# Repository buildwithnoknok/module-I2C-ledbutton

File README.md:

# noknok LED Button

A compact I²C‑controlled button module with integrated RGB LED backlight for the noknok ecosystem.  
Designed for user input, menu navigation, and illuminated UI feedback in modular builds.

---

## Overview

The **noknok LED Button** uses a **CH32V003F4U6** microcontroller to read a tactile push button and drive an **SK6812MINI-E** RGB LED via SPI+DMA. It connects to the Raspberry Pi Pico (Conductor) over the standard noknok **JST SH 4‑pin I²C connector**.

The I²C address is assigned dynamically at boot — no conflicts when using multiple modules on the same bus.

Typical use cases:
- Menu selection (OK / Back / Cancel)
- Illuminated status indicators
- Multi‑button control panels
- Confirm actions with colour feedback

---

## Features

- Dynamic I²C address via noknok enumeration protocol (no hardcoded address)
- CH32V003F4U6 microcontroller (RISC‑V, 48 MHz, QFN-20)
- SK6812MINI-E RGB LED (SPI + DMA driven — CPU-free updates)
- Tactile push button with 20 ms hardware debounce
- Press edge, release edge, and cumulative press count — no polling gaps
- 3.3V operation via noknok I²C connector
- Compact 20×20 mm PCB

---

## I²C Protocol

**I²C address:** assigned dynamically at boot — see [Enumeration](#enumeration).

### Commands (Pico → Module)

| Bytes | Command | Description |
|-------|---------|-------------|
| `0x00` | **LED OFF** | Turn LED off immediately |
| `0x10` `R` `G` `B` `0x00` | **SET COLOR** | Set LED colour (R, G, B each 0–255) |
| `0x11` | **RESET COUNT** | Reset cumulative press counter to 0 |
| `0xB0` | **ENTER BOOTLOADER** | Reset into the I²C bootloader for an over‑the‑wire firmware update (see [Firmware](#firmware)) |
| `0xB1` | **GET VERSION** | Standard noknok command — the next read returns 4 version bytes (see below) |

### Version read (Pico ← Module)

`GET_VERSION` (`0xB1`) is a **noknok ecosystem-standard** command (the `0xB0`–`0xBF` range is reserved for standard commands across every module). Write `0xB1`, then read **4 bytes**: `[PROTOCOL_VERSION, FW_MAJOR, FW_MINOR, FW_PATCH]` = `[0x01, 2, 2, 0]`. Lets the Conductor compare the installed version against the version required by the product manifest. **→ Full spec:** [Ecosystem / software / readme.md §5](https://github.com/buildwithnoknok/Ecosystem/blob/main/software/readme.md#5-standard-system-commands)

### Status read (Pico ← Module)

Read **2 bytes**:

**Byte 0 — status flags:**

| Bit | Meaning |
|-----|---------|
| 0 | Button currently pressed (`1` = held down) |
| 1 | Press event since last read (edge, auto-clears) |
| 2 | Release event since last read (edge, auto-clears) |

**Byte 1 — cumulative press count** (0–255, wraps)

> Edge flags (bits 1 and 2) are cleared on the module after each read. Poll at ~50 ms and you won't miss any press or release.

---

## Enumeration

The module uses the standard noknok dynamic enumeration protocol — no hardcoded I²C address. At boot it flashes the LED white briefly, then counts a UID-derived backoff delay before joining the bus at `0x7F` for address assignment. On successful assignment, the LED flashes green.

**→ Full protocol spec:** [Ecosystem / software / enumeration.md](https://github.com/buildwithnoknok/Ecosystem/blob/main/software/enumeration.md)

---

## Python API

Use the `noknok.py` library from the [Ecosystem repo](https://github.com/buildwithnoknok/Ecosystem/tree/main/software/pico) on the Pico.

```python
from noknok import Conductor

c = Conductor()        # GP8 = SDA, GP9 = SCL
c.enumerate()          # discover all modules (~3 s)

kb = c.ledbutton[0]             # first LED Button by discovery order
# or: kb = c.role["ok_button"]  # by role name after setup_roles()

# LED control
kb.set_color(255, 0, 0)         # red
kb.set_color(0, 255, 0)         # green
kb.set_color(255, 255, 255)     # white
kb.led_off()

# Button reading — returns LedButtonStatus or None on I2C error
s = kb.read()
if s is not None:
    print(s.pressed)        # True if held right now
    print(s.press_event)    # True if pressed since last read
    print(s.release_event)  # True if released since last read
    print(s.count)          # cumulative press count (0–255)

# Reset counter
kb.reset_count()
```

---

## Hardware

| Spec | Value |
|------|-------|
| PCB size | 20 × 20 mm |
| MCU | CH32V003F4U6 (QFN‑20, RISC‑V, 48 MHz) |
| LED | SK6812MINI-E (RGB, SPI-driven) |
| Button | Tactile switch, active LOW, internal pull-up |
| Connector | JST SH 4‑pin (Qwiic / STEMMA QT compatible) |
| Supply voltage | 3.3V via I²C connector |
| LED data pin | PC6 (SPI1 MOSI, DMA-driven) |
| Button pin | PD4 (active LOW) |
| I²C SDA | PC1 |
| I²C SCL | PC2 |
| Flash header | J3 — 3-pad pogo (GND, SWIO, VCC), noknok M2.5-keyed footprint. SWIO/PD1 also carries the status LED (D4, active LOW). |
| Hardware version | v2.0 |

---

## Firmware

**v2.4 runs under the shared noknok I²C bootloader** ([module-I2C-bootloader](https://github.com/buildwithnoknok/module-I2C-bootloader)), so the module can be re‑flashed **over the I²C bus** — no SWDIO cable needed in the field.

Flash map (16 KB):

| Region | Address | Written by |
|--------|---------|-----------|
| Bootloader — stage-0 (1 KB, frozen) + stage-1 (4 KB, OTA-updatable) | `0x0000` | SWD, **once** at manufacture |
| Application (this firmware) | `0x1400` | I²C OTA |
| Metadata (validity marker) | `0x3FC0` | I²C OTA |

The application is linked at the `0x1400` offset (`app.ld`, bootloader layout 2) and reserves the top 16 bytes of RAM for the bootloader handoff cell. Command `0xB0` drops the running module back into the bootloader for an update.

### Build

```bash
cd firmware/src
make build   # compile the offset-linked application -> keyboard_firmware.bin
```

> ch32fun must be installed at `../ch32fun/` relative to `firmware/src/` — see [cnlohr/ch32v003fun](https://github.com/cnlohr/ch32v003fun) for setup.

### Flashing

- **Normal (over I²C):** flash `keyboard_firmware.bin` from the Pico using the noknok flasher (`module_flasher.py` in `brain-Pico`). No cable.
- **First time / blank board:** SWD‑flash the bootloader once (`make flash` in the bootloader repo), then flash this app over I²C.
- **Backup / recovery (SWD):** the 5‑pin SWIO header is the unbrickable backstop — see *Recovery & SWD flashing* in the [bootloader README](https://github.com/buildwithnoknok/module-I2C-bootloader#recovery--swd-flashing).

`make flash` here still does a one‑off SWD flash of the app for bench bring‑up if you need it.

| Metric | Value |
|--------|-------|
| Firmware version | v2.4.1 (bootloader‑hosted, app base `0x1400`) |
| Application size | 3144 B (of the 10 KB app region) |

---

## Changelog

### Hardware v2.0 — status LED, pogo flash pads, no on-board pull-ups
Status LED on PD1/SWIO, castellated edges replaced with 3-pad pogo flashing pads (J3), on-board I²C pull-ups removed (host-only now). Full change record: [hardware/readme.md](hardware/readme.md#hardware-change-record).

### v2.4.1 — version bump only (firmware-index bring-up)
No functional change. Cut purely to give the new firmware-index OTA path a real installed-vs-current delta to exercise end to end (resolve → bootloader gate → fetch → flash → verify). Identical to v2.4.0 apart from the `GET_VERSION` patch byte. Ships alongside the first [`firmware/index.json`](firmware/index.json), which is how the brain now discovers the current firmware for this module — see [Ecosystem / software / firmware-index.md](https://github.com/buildwithnoknok/Ecosystem/blob/main/software/firmware-index.md).

### v2.4.0 — app base 0x1400 (bootloader layout 2)
Relinked at the `0x1400` flash offset (bootloader **layout 2**: 1 KB stage-0 + 4 KB stage-1 below the app; was `0x1000`). Firmware behaviour unchanged. **Not compatible with the legacy monolithic bootloader or a layout-1 stage-1** — such a module gets stage-0 + stage-1 v1.1.0 over SWD first, then this app over I²C. See [module-I2C-bootloader](https://github.com/buildwithnoknok/module-I2C-bootloader).

### v2.3.0 — watchdog + boot-health handshake (DEV-31)
Runs the independent watchdog (~2 s, kicked every main-loop pass) and writes `0` to `0x200007F8` the moment its I²C address is assigned — the app-health handshake with the stage-1 bootloader. Stage-1 counts watchdog resets and parks the module (error 7, rescued by the Conductor by UID) after three in a row, instead of booting a broken app forever. Contract: [Ecosystem / software / bootloader-update.md §3](https://github.com/buildwithnoknok/Ecosystem/blob/main/software/bootloader-update.md). No protocol or command change.

### v2.2.0 — SK6812 LED driver fix
Replaced the hand-rolled SPI+DMA SK6812 driver with cnlohr's proven
[`ws2812b_dma_spi_led_driver.h`](https://github.com/cnlohr/ch32fun/blob/master/extralibs/ws2812b_dma_spi_led_driver.h)
(ch32fun `extralibs`). The old driver produced a **marginal waveform** that
genuine-but-less-tolerant SK6812 lots misread — one batch showed wrong colours
(a spurious green channel) on ~13 of 20 units. This was **initially misdiagnosed
as bad/counterfeit LEDs; the LEDs are genuine OPSCO** — the fault was our driver.
The library produces a clean, glitch-free waveform. Four concrete differences vs.
the old driver:

- **16-bit SPI** transfers (was 8-bit) — cleaner framing, fewer inter-word gaps
- **`SPI1->HSCR = 1`** high-speed read mode (was not set)
- **`DMA_Priority_VeryHigh`** (was medium) — prevents inter-byte gaps under bus contention
- **`SPI1->DATAR = 0`** to force the data line low before the first frame (kills the start-of-frame glitch)

Still DMA (no bit-bang), so it never blocks the I²C / TIM2 interrupts. Wire order
(G, R, B) and the I²C command set are unchanged, so it's a drop-in OTA update.

### v2.1.0 — bootloader-hosted
Offset-linked at `0x1400` to run under the shared noknok I²C bootloader, enabling
I²C OTA firmware updates. Added the `GET_VERSION` (`0xB1`) standard command.

---

## Status

| Area | Status |
|------|--------|
| Hardware | v2.0 complete |
| Firmware | **v2.2 — complete (bootloader‑hosted, I²C OTA bench‑proven)** |
| Python library | **complete** (in [Ecosystem repo](https://github.com/buildwithnoknok/Ecosystem/tree/main/software/pico)) |
| Documentation | **complete** |

---

## License

- Firmware / code: MIT — see [LICENSE](LICENSE).
- Hardware (schematics, PCB layout, fab files): CC BY-SA 4.0 — see [LICENSE-hardware](LICENSE-hardware).

## Trademarks

**noknok** is a registered trademark in Switzerland (Swissreg 1300007033).

Qwiic is a registered trademark of SparkFun Electronics, Inc. STEMMA QT is a
trademark of Adafruit Industries, LLC. Both are named here only to state
connector compatibility - noknok is not affiliated with, endorsed by, or
sponsored by either company.
---

---

## Safety & Liability

noknok hardware is an electronic device and a DIY/maker kit. You assemble, modify, flash, power, and operate it at your own risk, and it is provided as is, without warranty. See the full notice: [License, Safety & Liability](https://buildwithnoknok.github.io/safety-and-license/).

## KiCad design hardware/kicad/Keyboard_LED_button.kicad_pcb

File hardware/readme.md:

# Hardware — noknok LED Button

Hardware design files for the noknok LED Button module (CH32V003F4U6 — I2C tactile button with RGB LED backlight).

- KiCad project: `kicad/Keyboard_LED_button.*`
- Schematic (PDF): `module-I2C-LEDButton_Schematics.pdf`
- BOM: `module_I2C-LEDButton.xls`
- Board renders: `module-I2C-ledbutton-front.png`, `module-I2C-ledbutton-back.png` *(pre-V2 renders — pending re-export)*

Hardware is licensed CC BY-SA 4.0 (see `../LICENSE-hardware`). Connector, flashing and mounting standards follow the [noknok Ecosystem guidelines](https://github.com/buildwithnoknok/Ecosystem) (electrical + mechanical).

---

## Hardware Change Record

### v2.0 — changes from v1.1
- **Status indicator LED on PD1** (in parallel with the SWIO flashing line — zero extra GPIO). Active-low: `+3V3_PROT → R5 (2.2 kΩ) → D4 anode; D4 cathode → PD1/SWIO`. Driven by the bootloader (off = app running, slow pulse = updating/recovering, solid = error). Parts: red 0603 LED (LCSC C2286) + 2.2 kΩ 0603 (LCSC C4190).
- **Removed the castellated edge pads** — both the I2C edge and the flashing edge (unreliable to contact). I2C is via the JST-SH (Qwiic) connectors J1/J2 only.
- **New flashing interface (J3)** — noknok flash pads (`noknok_FlashPads_I2C-module_1x3_M2.5`): 3 single-side SMD pogo pads (GND / SWIO / VCC) plus an embedded M2.5 keyed mounting hole, from the noknok KiCad library in the Ecosystem repo.
- **Second mounting hole (H1)** — plain `noknok_MountingHole_2.5mm_M2.5`, diagonally opposite the flash-pad hole.
- **Removed the on-board I²C pull-up resistors** (previously R1/R2) — pull-ups now live on the host (Conductor), not per module (avoids stacking on the shared bus). The host must provide the bus pull-ups (proposed 3.3 kΩ); a noknok pull-up PCB covers third-party hosts that lack them. See the [I²C Pull-up Resistor Strategy ADR](https://noknokdev.atlassian.net/wiki/spaces/SD/pages/82280449).
- **Remaining resistors renumbered** after the pull-ups were removed (values unchanged): VDD series R3→**R1** (10 Ω, no spike issue), LED current R4→**R2** (300 Ω), boost feedback divider R5/R6→**R3**/**R4** (25 kΩ / 10 kΩ). New status-LED resistor is **R5** (2.2 kΩ, see above).
- D1 (SK6812MINI-E RGB LED, payload), D2 (protection Zener) and D3 (boost-converter Schottky) are unchanged from v1.1.

**Gap vs. Knob/Buzzer V2 docs:** the board renders are still the pre-V2 photos, pending new production units.

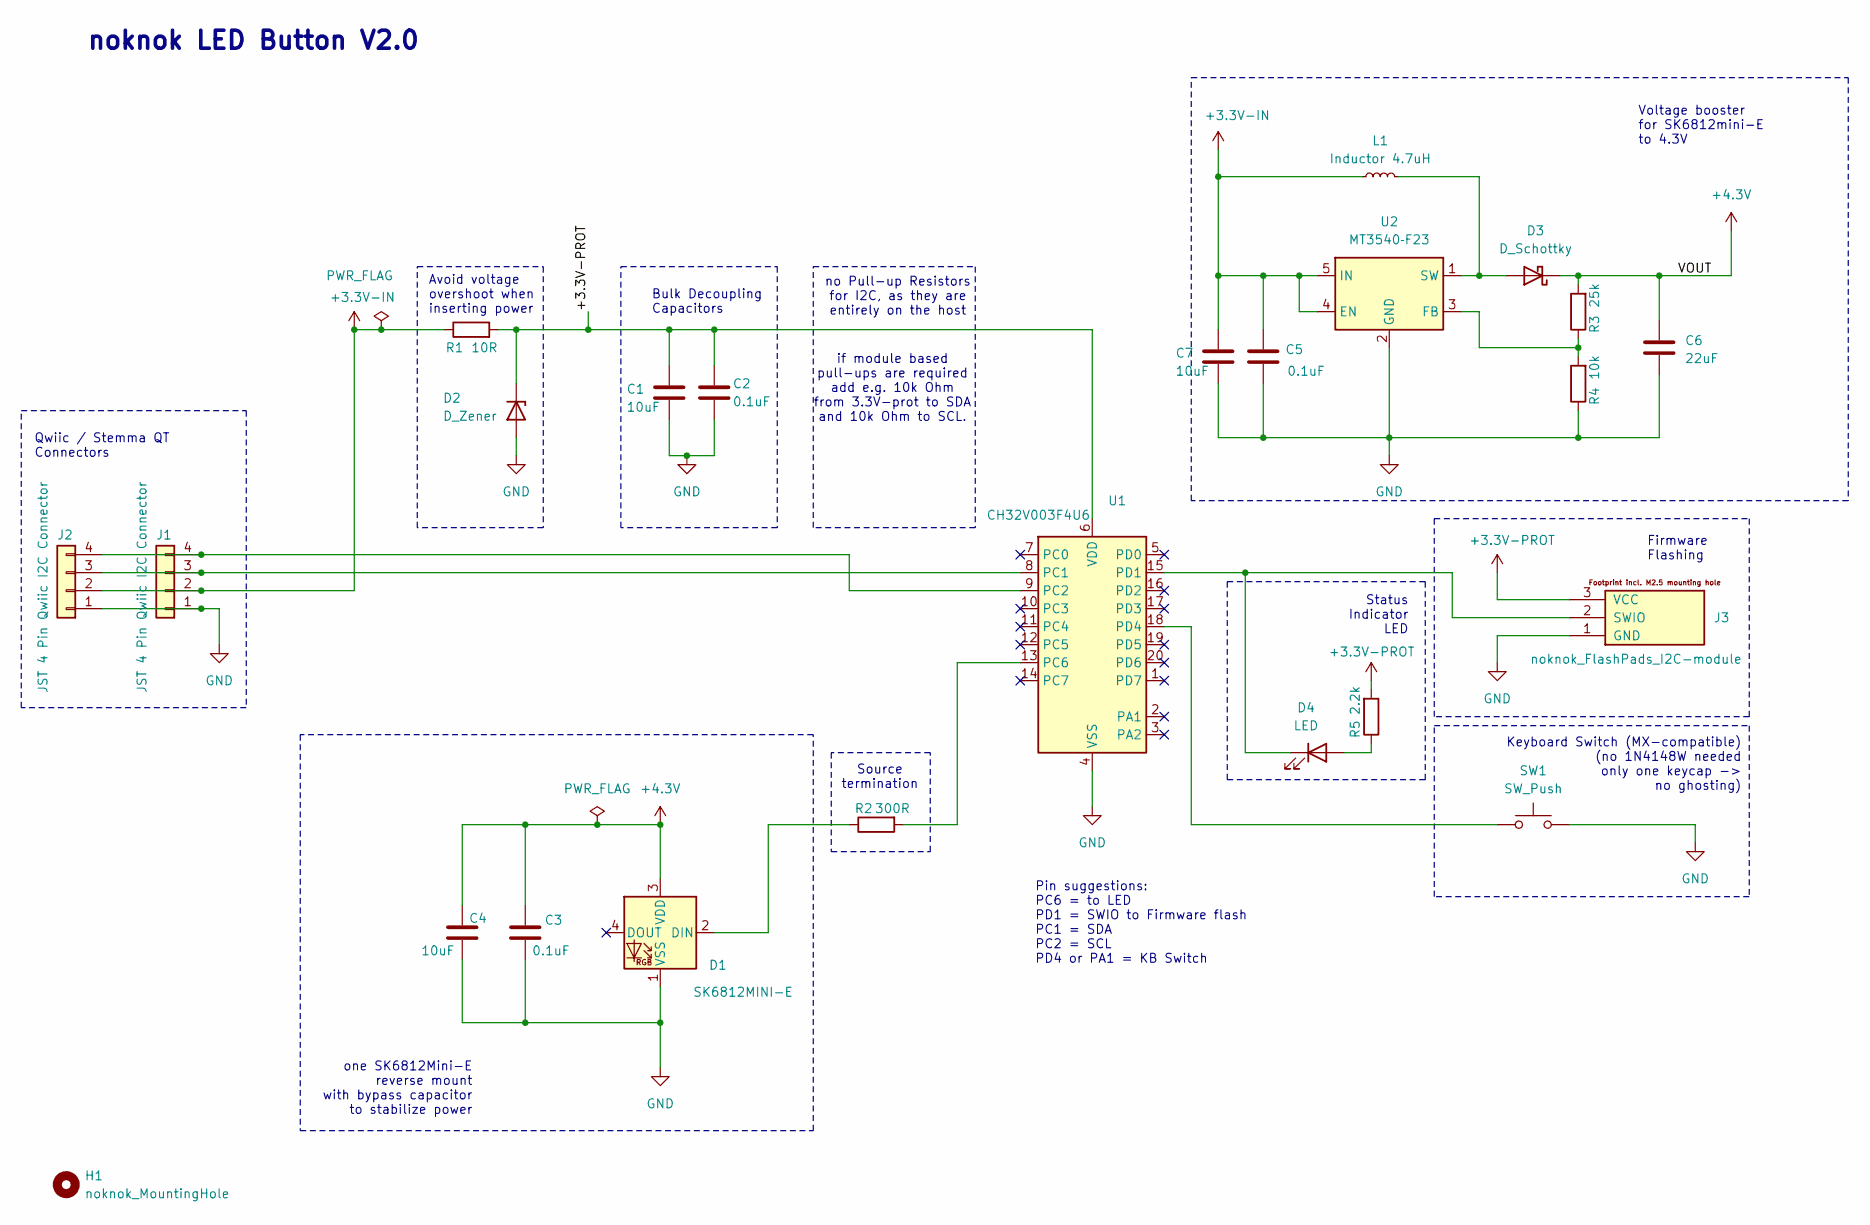
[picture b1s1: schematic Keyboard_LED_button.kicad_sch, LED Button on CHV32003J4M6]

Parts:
C1, C4, C7: 10uF; C_0603_1608Metric
C2, C3, C5: 0.1uF; C_0603_1608Metric
C6: 22uF; C_0603_1608Metric
D1: SK6812MINI-E; LED_SK6812MINI-E_3.2x2.8mm_P1.5mm_ReverseMount
D2: D_Zener; D_SOD-323
D3: D_Schottky; D_SOD-323
D4: LED; LED_0603_1608Metric
H1: noknok_MountingHole; noknok_MountingHole_2.5mm_M2.5
J1, J2: JST 4 Pin Qwiic I2C Connector; JST_SH_SM04B-SRSS-TB_1x04-1MP_P1.00mm_Horizontal
J3: noknok_FlashPads_I2C-module; noknok_FlashPads_I2C-module_1x3_M2.5
L1: Inductor 4.7uH; L_Changjiang_FTC252010S
R1: 10R; R_0603_1608Metric
R2: 300R; R_0603_1608Metric
R3: 25k; R_0603_1608Metric
R4: 10k; R_0603_1608Metric
R5: 2.2k; R_0603_1608Metric
SW1: SW_Push; SW_Cherry_MX_1.00u_PCB_CHRIS
U1: CH32V003F4U6; QFN-20-1EP_3x3mm_P0.4mm_EP1.65x1.65mm
U2: MT3540‑F23; SOT-23-5

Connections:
+3.3V-IN: C5.1, C7.1, J1.2, J2.2, L1.1, R1.1, U2.4 (EN), U2.5 (IN)
+3.3V-PROT: C1.1, C2.1, D2.1 (K), J3.3 (VCC), R1.2, R5.2, U1.6 (VDD)
+4.3V: C3.1, C4.1, C6.1, D1.3 (VDD), D3.1 (K), R3.2
GND: C1.2, C2.2, C3.2, C4.2, C5.2, C6.2, C7.2, D1.1 (VSS), D2.2 (A), J1.1, J2.1, J3.1 (GND), R4.1, SW1.1, U1.4 (VSS), U1.21 (VSS), U2.2 (GND)
unnamed: D1.2 (DIN), R2.1
unnamed: D3.2 (A), L1.2, U2.1 (SW)
unnamed: D4.2 (A), R5.1
unnamed: D4.1 (K), J3.2 (SWIO), U1.15 (PD1)
unnamed: J1.3, J2.3, U1.8 (PC1)
unnamed: J1.4, J2.4, U1.9 (PC2)
unnamed: R2.2, U1.13 (PC6)
unnamed: SW1.2, U1.18 (PD4)
unnamed: R3.1, R4.2, U2.3 (FB)

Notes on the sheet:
Voltage booster for SK6812mini-E to 4.3V
if module based pull-ups are required add e.g. 10k Ohm from 3.3V-prot to SDA and 10k Ohm to SCL.
Avoid voltage overshoot when inserting power
noknok LED Button V2.0
Pin suggestions: PC6 = to LED PD1 = SWIO to Firmware flash PC1 = SDA PC2 = SCL PD4 or PA1 = KB Switch
no Pull-up Resistors for I2C, as they are entirely on the host
Status Indicator LED
Firmware Flashing
Source termination
Qwiic / Stemma QT Connectors
Bulk Decoupling Capacitors
Keyboard Switch (MX-compatible) (no 1N4148W needed only one keycap -> no ghosting)
one SK6812Mini-E reverse mount with bypass capacitor to stabilize power

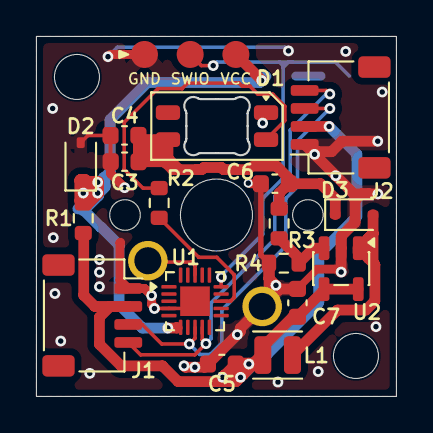
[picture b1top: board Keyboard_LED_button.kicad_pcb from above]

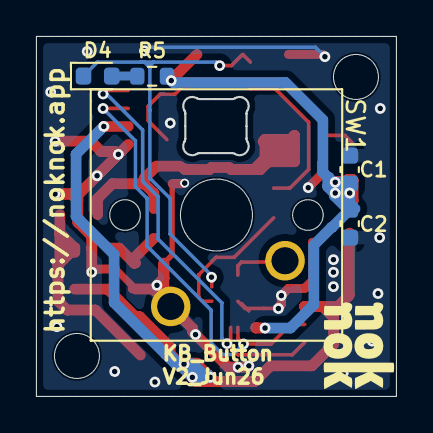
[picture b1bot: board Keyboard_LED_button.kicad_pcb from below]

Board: 2 copper layers, 20.0 x 20.0 mm, 24 parts (5 on the bottom side), 13 nets.

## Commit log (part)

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2026-05-08 Create hardware folder
2026-05-08 add schematics
2026-05-08 Create hardware/kicad folder
2026-05-08 Upload Kicad project files
2026-05-08 Create firmware folder
2026-05-08 Create firmware/src folder
2026-05-08 Create firmware/bin folder
2026-05-08 Create docs folder
2026-06-01 Update product name to # noknok LED Button
2026-06-01 firmware: add keyboard button module firmware v1.0
    - CH32V003F4U6 (QFN-20)
    - SK6812MINI-E RGB LED via SPI+DMA (PC6=SPI1_MOSI, 3MHz, GRB only)
    - Button on PD4 with 20ms debounce
    - noknok enumeration protocol v3.1 (MODULE_TYPE=0x03)
    - I2C protocol: set LED colour, read button state + press count
2026-06-01 docs: full README rewrite - correct MCU, LED, protocol, enumeration, Python API, firmware status
2026-06-01 Added product images
2026-06-01 docs: remove enumeration detail, link to Ecosystem/software/enumeration.md
2026-06-09 Add released firmware binary to firmware/bin
    Track the distributable offset-linked app image (flashed over I2C by the
    Pico). Adds a .gitignore exception so firmware/bin/*.bin is versioned while
    build artifacts elsewhere stay ignored.
2026-06-10 Update README.md
    updated img path
2026-06-10 firmware v2.1: add GET_VERSION (0xB1) standard command (DEV-1)
2026-06-10 Update released firmware binary for GET_VERSION (DEV-1)
2026-06-11 Add MIT + CC BY-SA 4.0 licenses and License/Safety README sections for public release
2026-06-15 hardware: add hardware/readme.md with v2.0 change record
    v2.0 changes from v1.1: status LED on PD1, optional custom-button thru-holes,
    removed castellated edges, noknok M2.5 mounting holes + flashing pads. (Pull-up change
    deferred pending host-side decision.)
2026-06-15 hardware: v2.0 removes on-board I2C pull-ups (moved to host per pull-up ADR)
2026-06-16 hardware: drop custom-button thru-holes from v2.0 record (did not fit V2; tracked as DEV-10)
2026-06-16 LED Button V2 hardware: updated KiCad schematic + PCB; add V2 + V1.1 schematic PDFs
    Updated Keyboard_LED_button KiCad project (schematic + board) for v2.0; added
    Schematics_LEDButton_V2_20260616.pdf and renamed-as Schematics_LEDButton_V1_1_20260408.pdf;
    removed obsolete Schematics_Keyboard_Button_20260408.pdf and .keep placeholders.
2026-06-23 chore: remove redundant firmware/.keep (folder now has content)
2026-06-23 chore: remove redundant firmware/bin/.keep (folder now has content)
2026-06-23 chore: remove redundant firmware/src/.keep (folder now has content)
